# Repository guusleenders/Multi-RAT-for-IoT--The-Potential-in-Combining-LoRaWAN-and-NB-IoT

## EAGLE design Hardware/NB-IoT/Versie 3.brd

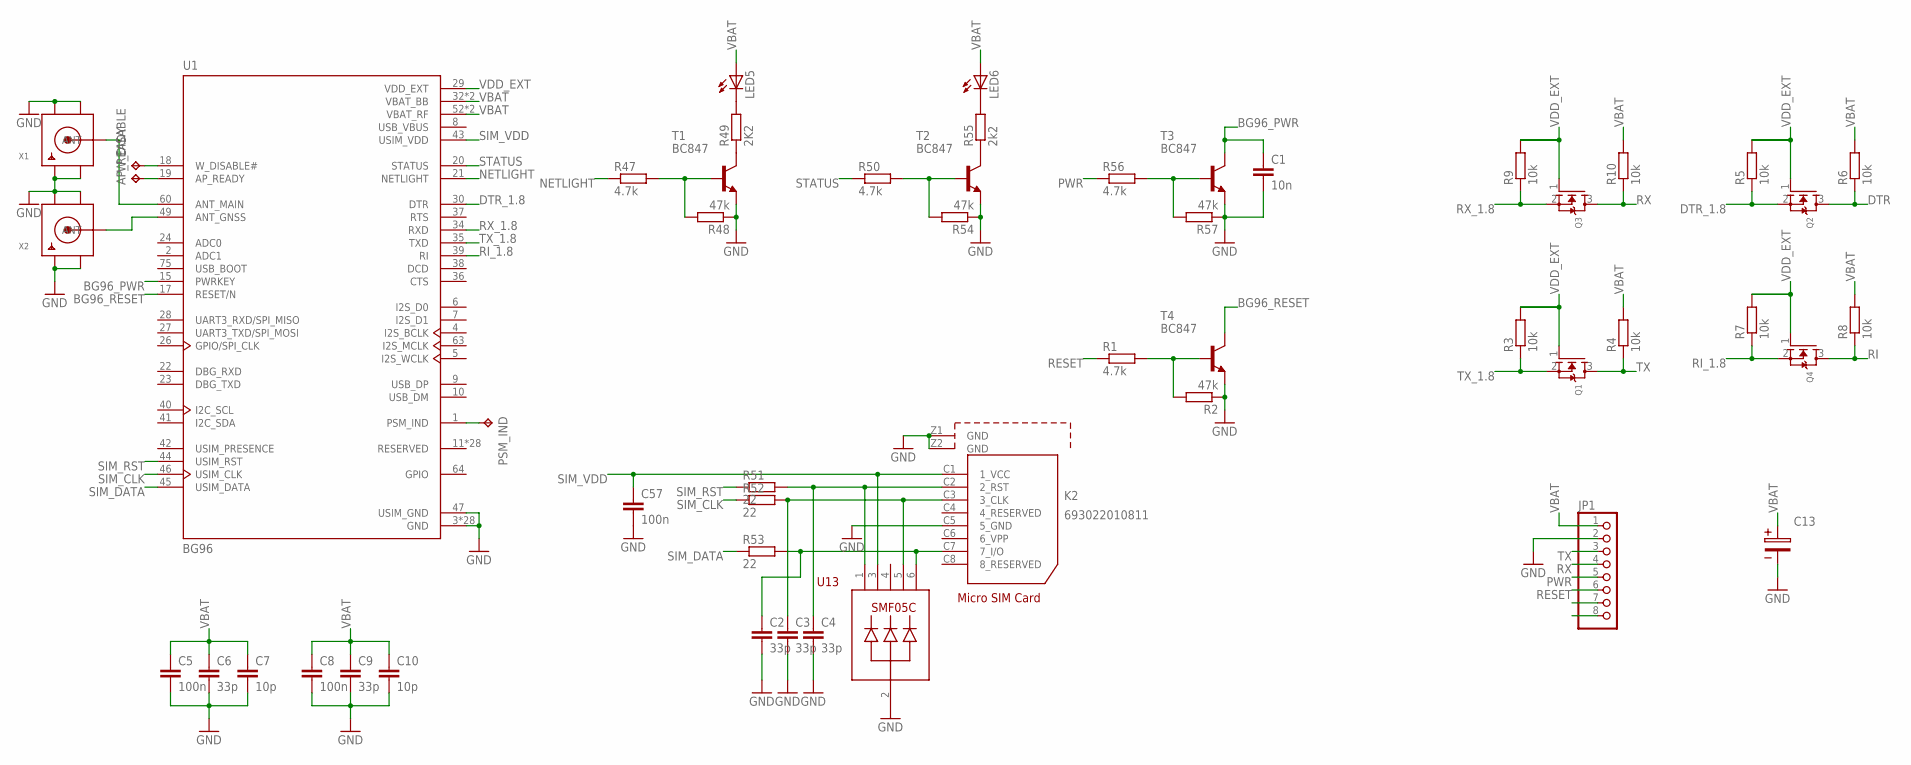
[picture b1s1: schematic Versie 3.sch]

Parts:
AP_READY: TPTP10R; TP10R
C1: 10n; C0603
C2, C3, C4, C6, C9: 33p; C0603
C5, C8, C57: 100n; C0603
C7, C10: 10p; C0603
C13: WCAP-ASLI_6,3X7,7_865080545012; 3.5X1.6X2.1(BXCXA)
JP1: PINHD-1X8; 1X08
K2: 693022010811
LED5, LED6: LEDCHIPLED_0805; CHIPLED_0805
PSM_IND: TPTP10R; TP10R
Q1, Q2, Q3, Q4: MOSFET-NREFLOW; SOT23
R1, R47, R50, R56: 4.7k; R0603
R2, R48, R54, R57: 47k; R0603
R3, R4, R5, R6, R7, R8, R9, R10: 10k; R0603
R49: 2K2; R0603
R51, R52, R53: 22; R0603
R55: 2k2; R0603
T1, T2, T3, T4: BC847; SOT23
U1: BG96; LTE_MODULE_BG96
U13: SMF05C; SC-70-6
W_DISABLE: TPTP10R; TP10R
X1, X2: SMACONNECTOR_EDGE_UFL; SMA_EDGELAUNCH_UFL

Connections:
BG96_PWR: C1.1, T3.3 (C), U1.15 (PWRKEY)
BG96_RESET: T4.3 (C), U1.17 (RESET/N)
DTR: JP1.7, Q2.3 (D), R6.1
DTR_1.8: Q2.2 (S), R5.1, U1.30 (DTR)
GND: C1.2, C2.2, C3.2, C4.2, C5.2, C6.2, C7.2, C8.2, C9.2, C10.2, C13.2, C57.2, JP1.2, K2.C5 (5_GND), K2.Z1 (GND), K2.Z2 (GND), R2.1, R48.1, R54.1, R57.1, T1.2 (E), T2.2 (E), T3.2 (E), T4.2 (E), U1.3 (GND), U1.31 (GND), U1.47 (USIM_GND), U1.48 (GND), U1.50 (GND), U1.54 (GND), U1.55 (GND), U1.58 (GND), U1.59 (GND), U1.61 (GND), U1.62 (GND), U1.67 (GND), U1.68 (GND), U1.69 (GND), U1.70 (GND), U1.71 (GND), U1.72 (GND), U1.73 (GND), U1.74 (GND), U1.79 (GND), U1.80 (GND), U1.81 (GND), U1.82 (GND), U1.89 (GND), U1.90 (GND), U1.91 (GND), U1.100 (GND), U1.101 (GND), U1.102 (GND), U13.2, X1.GND@1 (GND1), X1.GND@2 (GND2), X1.GND@3 (GND3), X1.GND@4 (GND4), X2.GND@1 (GND1), X2.GND@2 (GND2), X2.GND@3 (GND3), X2.GND@4 (GND4)
unnamed: U1.60 (ANT_MAIN), X1.P (ANT)
unnamed: U1.49 (ANT_GNSS), X2.P (ANT)
unnamed: R1.2, R2.2, T4.1 (B)
unnamed: AP_READY.TP, U1.19 (AP_READY)
unnamed: U1.18 (W_DISABLE#), W_DISABLE.TP
unnamed: R56.2, R57.2, T3.1 (B)
unnamed: C4.1, K2.C2 (2_RST), R51.2, U13.1
unnamed: C3.1, K2.C3 (3_CLK), R52.2, U13.5
unnamed: C2.1, K2.C7 (7_I/O), R53.2, U13.6
unnamed: R47.2, R48.2, T1.1 (B)
unnamed: R49.1, T1.3 (C)
unnamed: LED5.C, R49.2
unnamed: R50.2, R54.2, T2.1 (B)
unnamed: R55.1, T2.3 (C)
unnamed: LED6.C, R55.2
NETLIGHT: R47.1, U1.21 (NETLIGHT)
PSM_IND: PSM_IND.TP, U1.1 (PSM_IND)
PWR: JP1.5, R56.1
RESET: JP1.6, R1.1
RI: JP1.8, Q4.3 (D), R8.1
RI_1.8: Q4.2 (S), R7.1, U1.39 (RI)
RX: JP1.4, Q3.3 (D), R10.1
RX_1.8: Q3.2 (S), R9.1, U1.34 (RXD)
SIM_CLK: R52.1, U1.46 (USIM_CLK)
SIM_DATA: R53.1, U1.45 (USIM_DATA)
SIM_RST: R51.1, U1.44 (USIM_RST)
SIM_VDD: C57.1, K2.C1 (1_VCC), U1.43 (USIM_VDD), U13.3
STATUS: R50.1, U1.20 (STATUS)
TX: JP1.3, Q1.3 (D), R4.1
TX_1.8: Q1.2 (S), R3.1, U1.35 (TXD)
USB_VBUS: U1.8 (USB_VBUS)
VBAT: C5.1, C6.1, C7.1, C8.1, C9.1, C10.1, C13.1, JP1.1, LED5.A, LED6.A, R4.2, R6.2, R8.2, R10.2, U1.32 (VBAT_BB), U1.33 (VBAT_BB), U1.52 (VBAT_RF), U1.53 (VBAT_RF)
VDD_EXT: Q1.1 (G), Q2.1 (G), Q3.1 (G), Q4.1 (G), R3.2, R5.2, R7.2, R9.2, U1.29 (VDD_EXT)

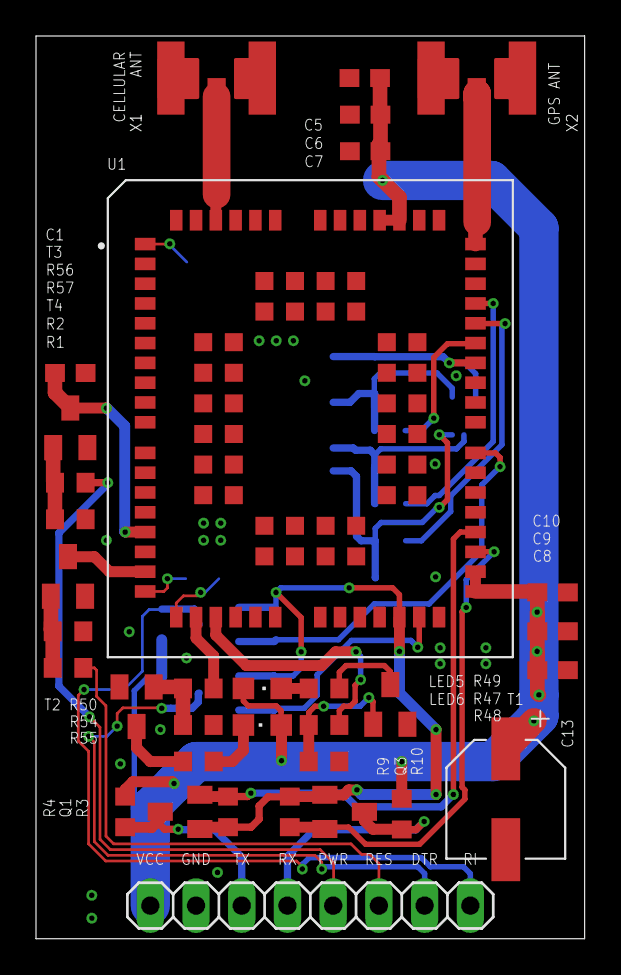
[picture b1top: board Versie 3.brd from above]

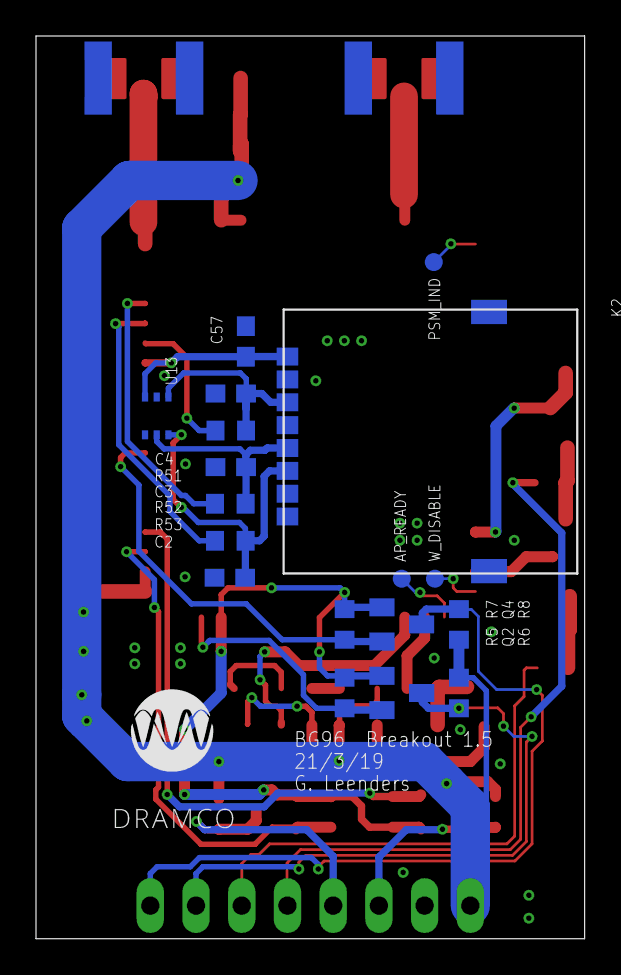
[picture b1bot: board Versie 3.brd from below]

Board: 2 copper layers, 30.5 x 50.2 mm, 52 parts (18 on the bottom side), 37 nets.

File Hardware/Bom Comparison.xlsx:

BOM Comparison Multi-RAT (Estimate cost)
 | # | Price USD (>1pcs) | Total cost | Octopart link
NB-IoT
BG96MA-128-SGN | 1 | 19 | 19 | https://octopart.com/bg96ma-128-sgn-quectel-94178001?r=sp
WR-CRD Micro SIM Card Connector | 1 | 1.64 | 1.64 | https://octopart.com/693022010811-w%C3%BCrth+elektronik-5264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
BC847W,115 | 4 | 0.13 | 0.52 | https://octopart.com/bc847w%2C115-nexperia-78739125?r=sp
DMN2310UW-7 | 4 | 0.06 | 0.24 | https://octopart.com/dmn2310uw-7-diodes+inc.-112906842?r=sp
Antenna | 1 | 5.05 | 5.05 | https://octopart.com/ant-ghel2r-sma-rf+solutions-28336341?r=sp
Resistors and Capacitors | 32 | 0.01 | 0.32
Total |  |  | 26.77
LoRaWAN
RN2483A-I/RM104 | 1 | 13.44 | 13.44 | https://octopart.com/rn2483a-i%2Frm104-microchip-90584481?r=sp
Antenna | 1 | 3.2080000000000002 | 3.2080000000000002 | https://octopart.com/105262-0001-molex-29198908?r=sp
Resistors and Capacitors | 8 | 0.01 | 0.08
Total |  |  | 16.727999999999998
Common
EFM32HG322F64G-B-QFP48 | 1 | 2.4129999999999998 | 2.4129999999999998 | https://octopart.com/efm32hg322f64g-b-qfp48-silicon+labs-756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
LFXTAL050789CUTT | 1 | 0.79 | 0.79 | https://octopart.com/lfxtal050789cutt-iqd+frequency+products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
7A-24.000MAAJ-T | 1 | 0.72 | 0.72 | https://octopart.com/7a-24.000maaj-t-txc-18785507?r=sp
MCP73831T-2ATI/OT | 1 | 0.59 | 0.59 | https://octopart.com/mcp73831t-2ati%2Fot-microchip-422780?r=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
USB Connector | 1 | 0.92 | 0.92 | https://octopart.com/47346-0001-molex-7164928?r=sp
Li-Po Battery | 1 | 10 | 10
Resistors and Capacitors | 15 | 0.01 | 0.15
Total |  |  | 15.583
NB-IoT only solution |  |  | 42.353000000000002
LoRaWAN only solution |  |  | 32.311
Multi-RAT solution |  |  | 59.081000000000003

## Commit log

2021-06-17 Changed file names
2021-07-02 Added BOM comparison
2021-07-05 Added measurement files

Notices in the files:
parts and their libraries:
Kondensatoren: Copyright: Würth Elektronik
